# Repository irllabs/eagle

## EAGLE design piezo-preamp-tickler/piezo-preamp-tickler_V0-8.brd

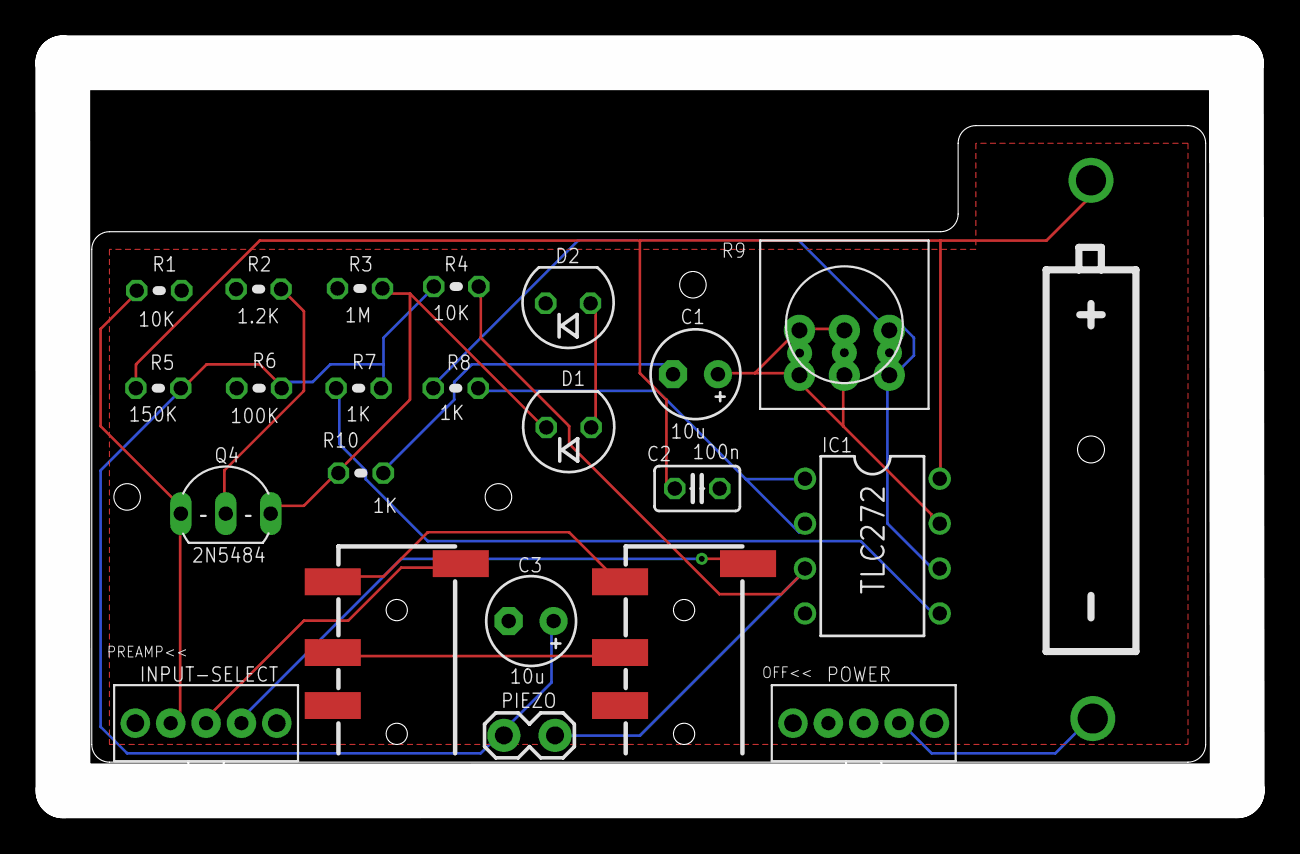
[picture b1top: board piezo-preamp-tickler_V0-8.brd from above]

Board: 2 copper layers, 66.4 x 41.2 mm, 23 parts (0 on the bottom side), 18 nets.

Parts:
BAT1: BATTERY-A23
C1, C3: 10u; E2,5-5
C2: 100n; C025-025X050
D1, D2: BB112; SOT54H
IC1: TLC272; DIL08
INPUT-SELECT: SPDT-SWITCH
ON/OFF: labl; SPDT-SWITCH
PIEZO: 1X02_LOCK
Q4: 2N5484; TO92-
R1, R4: 10K; 0204V
R2: 1.2K; 0204V
R3: 1M; 0204V
R5: 150K; 0204V
R6: 100K; 0204V
R7, R8, R10: 1K; 0204V
R9: TRIM-3386
TO-HEADSET: AUDIO-JACK3LGPADS; AUDIO-JACK-TRRS-SMD
TO-PHONE: AUDIO-JACK3LGPADS; AUDIO-JACK-TRRS-SMD

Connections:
GND: C2.1, C3.-, D2.C, IC1.4, ON/OFF.2, R1.1, R2.1, R3.1, R6.1, TO-HEADSET.RING2, TO-PHONE.RING2
unnamed: D1.A, D2.A
unnamed: BAT1.GND@1, ON/OFF.3
unnamed: Q4.2, R2.2
unnamed: IC1.5, R7.1
unnamed: C1.+, IC1.7, R9.1, R9.2, R9.4, R9.5
unnamed: IC1.6, R8.2, R9.3, R9.6
unnamed: C3.+, PIEZO.2, R4.2, R5.1, R6.2, R7.2
unnamed: IC1.3, PIEZO.1, R4.1
unnamed: D1.C, Q4.1, R3.2, R10.1
unnamed: C1.-, R10.2
unnamed: INPUT-SELECT.3, TO-HEADSET.EARTH
unnamed: TO-HEADSET.TIP, TO-PHONE.TIP
unnamed: IC1.1, IC1.2, R8.1
unnamed: TO-HEADSET.RING1, TO-PHONE.RING1
TO-PHONE: INPUT-SELECT.2, TO-PHONE.EARTH
V9V: BAT1.PWR@1, C2.2, IC1.8, R5.2
`DEL: INPUT-SELECT.1, Q4.3, R1.2

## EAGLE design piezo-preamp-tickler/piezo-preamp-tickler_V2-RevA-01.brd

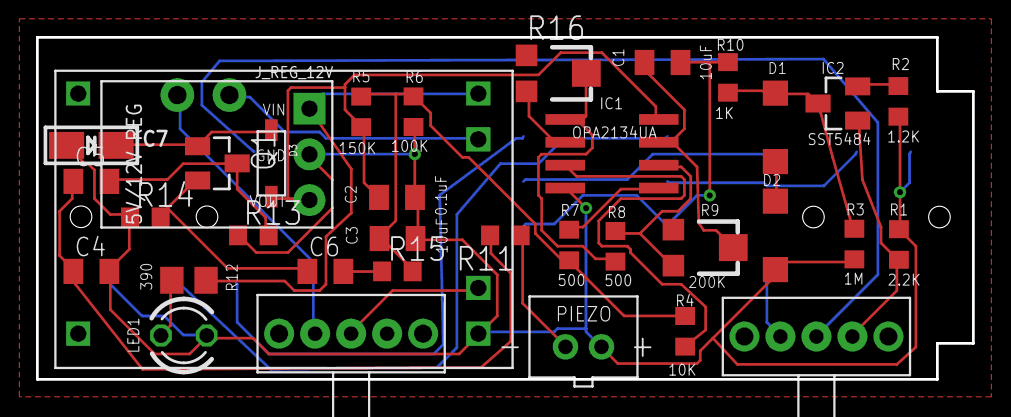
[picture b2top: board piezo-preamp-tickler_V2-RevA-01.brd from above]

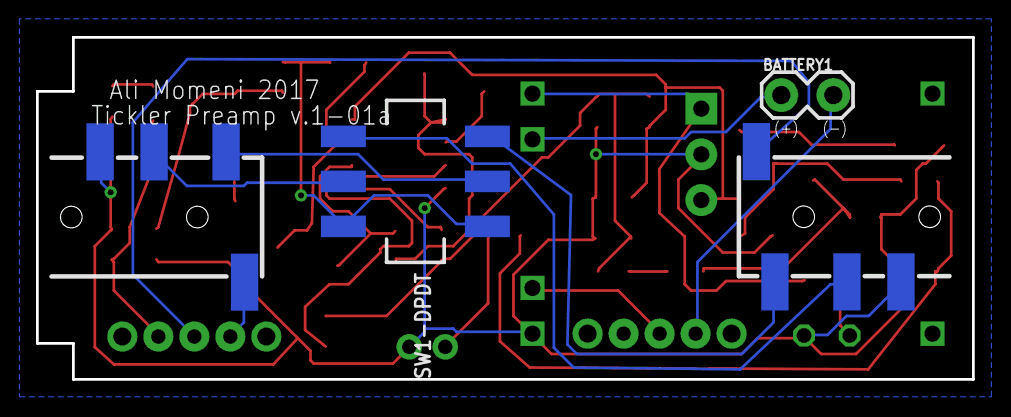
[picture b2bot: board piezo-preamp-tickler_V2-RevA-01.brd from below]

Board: 2 copper layers, 52.0 x 19.0 mm, 39 parts (4 on the bottom side), 31 nets.

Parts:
BATTERY1: 1X02_LOCK
C1, C3: 10uF; C0805K
C2: 0.1uF; C0805K
C4: 10p; C0805K
C5, C6: 0.033u; C0805K
C7: 3.3U; EIA3216-18/A-R
D1, D2: SOD123
D3: 1N4148; SOD-123
IC1: OPA2134UA; SO08
IC2: SST5484; SOT23
J_REG_12V: POLOLU_VOLTAGE_REGULATORS_3PIN; POLOLU_5V-12V_STEPUP_U3V12F5-U3V12F12
LED1: LED3MM
PIEZO: JST-PH-2-THM
POWER: SPDT; SWITCH_SPDT-TE-CONNECT
Q1: SST201; SOT23
R1: 2.2K; R0603
R2: 1.2K; R0603
R3: 1M; R0603
R4: 10K; R0603
R5: 150K; R0603
R6, R11: 100K; R0603
R7, R8: 500; R0603
R9, R16: 200K; TC33X
R10: 1K; R0603
R12: 390; R0805
R13: 10M; R0603
R14: 220K; R0603
R15: 13K; R0603
SW1-DPDT: OUTPUT-select; DPDT_SMT_JS202011SCQN
SW2-SPST: INPUT-select; SWITCH_SPDT-TE-CONNECT
TO-HEADSET: AUDIO-JACK3LGPADS; AUDIO-JACK-TRRS-SMD
TO-PHONE: AUDIO-JACK3LGPADS; AUDIO-JACK-TRRS-SMD
USB-LIPO-CHARGER: TP4056-MODULE; TP4056-LITHIUM-PROTECTED-MODULE

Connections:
+12V: C2.1, D3.A, IC1.8, J_REG_12V.VOUT, R5.2
GND: C2.2, C3.2, C4.2, C7.-, D2.C, IC1.4, J_REG_12V.GND, LED1.K, PIEZO.1, R1.1, R2.1, R3.1, R6.1, R13.1, R14.1, TO-HEADSET.RING2, TO-PHONE.RING2, USB-LIPO-CHARGER.OUT-
unnamed: D1.A, D2.A
unnamed: PIEZO.2, R11.1
unnamed: IC2.2, R2.2
unnamed: IC1.5, R7.1
unnamed: C1.1, IC1.7, R9.2
unnamed: IC1.6, R8.2, R9.3
unnamed: C3.1, R4.2, R5.1, R6.2, R7.2, R15.2
unnamed: IC1.3, R4.1
unnamed: D1.C, IC2.3, R3.2, R10.1
unnamed: C1.2, R10.2, SW1-DPDT.P$3, SW1-DPDT.P$4
unnamed: SW2-SPST.1, TO-HEADSET.EARTH
unnamed: SW1-DPDT.P$5, TO-HEADSET.TIP
unnamed: IC1.1, R8.1, R16.2
unnamed: SW1-DPDT.P$2, TO-HEADSET.RING1
unnamed: C4.1, C5.1, R11.2
unnamed: SW2-SPST.2, TO-PHONE.EARTH
unnamed: LED1.A, R12.1
unnamed: BATTERY1.1, USB-LIPO-CHARGER.B+
unnamed: POWER.2, USB-LIPO-CHARGER.B-
unnamed: BATTERY1.2, POWER.1
unnamed: C5.2, Q1.3, R13.2
unnamed: C6.1, Q1.2, R14.2
unnamed: C6.2, R15.1
unnamed: C7.+, D3.C, Q1.1
unnamed: SW1-DPDT.P$1, TO-PHONE.RING1
unnamed: SW1-DPDT.P$6, TO-PHONE.TIP
unnamed: IC1.2, R16.3
SELECT: IC2.1, R1.2, SW2-SPST.3
VBAT: J_REG_12V.VIN, R12.2, USB-LIPO-CHARGER.OUT+

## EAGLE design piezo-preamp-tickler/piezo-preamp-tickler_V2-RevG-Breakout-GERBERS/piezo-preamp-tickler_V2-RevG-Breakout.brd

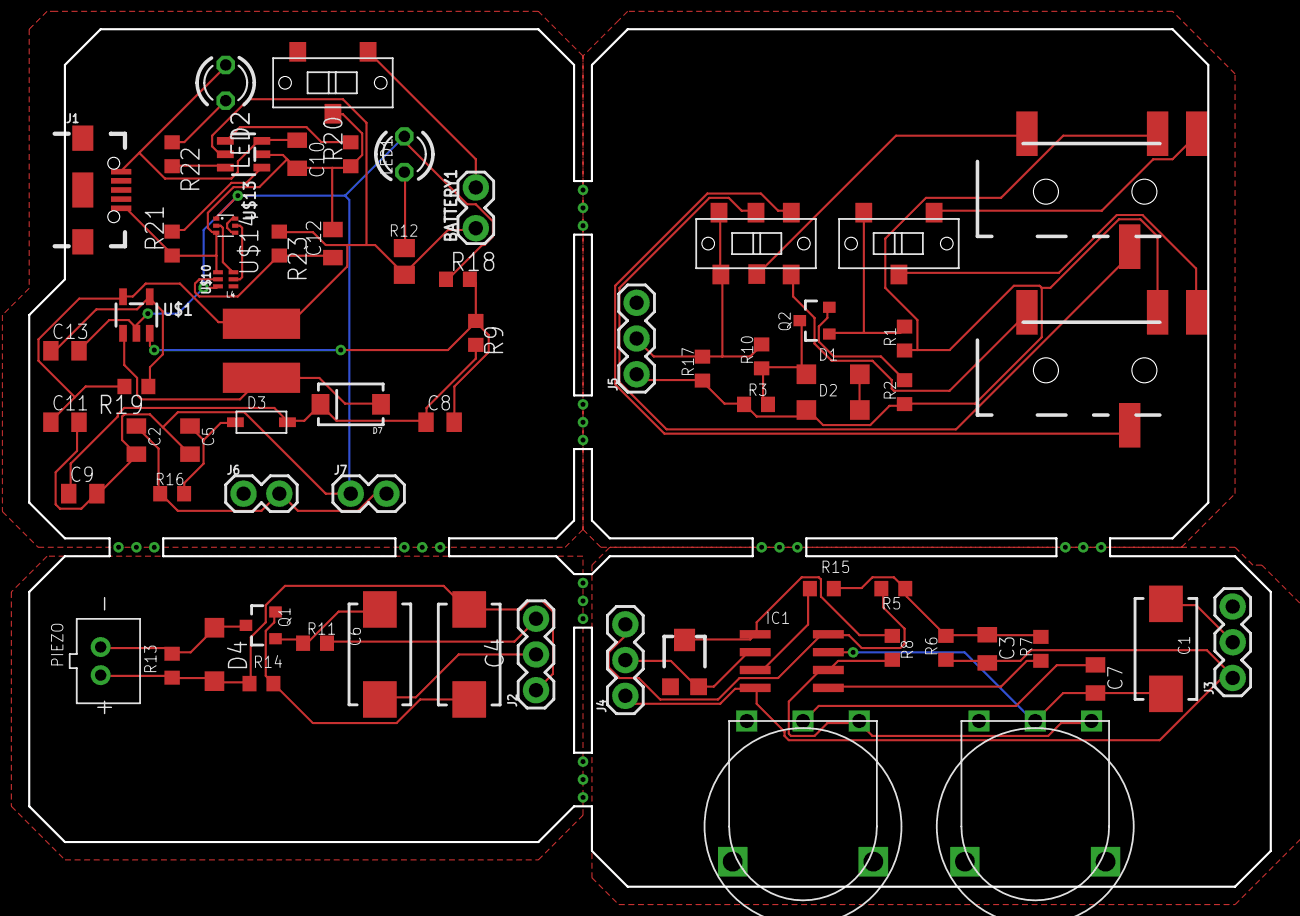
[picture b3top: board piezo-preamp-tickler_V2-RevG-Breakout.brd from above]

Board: 2 copper layers, 88.3 x 61.0 mm, 67 parts (0 on the bottom side), 49 nets.

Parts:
BATTERY1: 1X02_LOCK
C1: 47uF; CT7343
C2, C12, C13: 0.1uF; C0805K
C3, C5, C7, C9, C10, C11: 10uF; C0805K
C4: 150uF; CT7343
C6: 3.3uF; CT7343
C8: 22pF; C0805K
D1, D2, D4: SOD123
D3: 1N4148; SOD-123
D7: 10BQ015; SMA-DIODE
IC1: OPA2134UA; SO08
J1: USB-B-MICRO-SMD_RED_PASTE
J2, J3, J4, J5: 1X03
J6, J7: 1X02
L4: 2.7uH; CR54
LED1, LED2: LED3MM
PIEZO: JST-PH-2-THM
POWER: SPDT; SWITCH_SPDT_CL-SB-12B
Q1, Q2: J201SOT-23; SOT23-3
R1: 2.2K; R0603
R2, R14: 1.2K; R0603
R3: 1M; R0603
R4: 20K; TC33X
R5: 100K; R0603
R6: 150K; R0603
R7, R8, R10, R15: 1K; R0603
R9: 866k; R0603
R11, R17: 10K; R0603
R12: 390; R0805
R13: 10M; R0603
R16: 10; R0603
R18: 100k; R0603
R19: 15k; R0603
R20, R21: 10k; R0603
R22: 1k; R0603
R23: 330; R0603
SW2-SPST: INPUT-select; SWITCH_SPDT_CL-SB-12B
TO-HEADSET: AUDIO-JACK3LGPADS; AUDIO-JACK-TRRS-SMD
TO-PHONE: AUDIO-JACK3LGPADS; AUDIO-JACK-TRRS-SMD
U$1: SC4503; SOT23-5
U$2: SWITCH_DPDT; SWITCH_DPDT_CL-SB-22B
U$4, U$5: THUMBPOT14
U$10: BQ297X-BATTERY-MANAGER; WSON-6
U$13: BQ21040-LIPO-CHARGER; SOT23-6
U$14: DUAL-NFET-DMN2400; SOT-563

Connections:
+12V: C8.1, C9.1, D3.A, D7.C, R9.2
GND: C2.2, C5.2, C9.2, C11.2, C13.2, J7.1, LED1.K, R18.1, U$1.2, U$10.6, U$14.1
GND1: C10.2, C12.2, J1.GND, POWER.P$2, R20.1, R21.1, U$10.4, U$13.5, U$14.3
unnamed: D1.A, D2.A
unnamed: D4.C, PIEZO.2, Q1.3, R13.2
unnamed: Q2.2, R2.2
unnamed: IC1.5, R7.1
unnamed: C1.+, C7.2, IC1.7, U$4.P$2
unnamed: IC1.6, R8.2, U$4.P$1, U$5.P$1
unnamed: C6.+, Q1.1, R11.1
unnamed: D1.C, Q2.3, R3.2, R10.1
unnamed: J5.2, R10.2, R17.2, U$2.1, U$2.4
unnamed: SW2-SPST.P$1, TO-HEADSET.EARTH
unnamed: TO-HEADSET.TIP, U$2.2
unnamed: C4.+, Q1.2, R14.2
unnamed: TO-HEADSET.RING1, U$2.5
unnamed: C5.1, D3.C, R16.2
unnamed: SW2-SPST.P$2, TO-PHONE.EARTH
unnamed: LED1.A, R12.1
unnamed: IC1.2, J4.2, R4.3
unnamed: BATTERY1.2, POWER.P$1
unnamed: IC1.3, R15.1
unnamed: C3.1, R5.1, R6.2, R7.2, R15.2
unnamed: IC1.1, R4.2, R8.1
unnamed: J2.3, R11.2
unnamed: TO-PHONE.RING1, U$2.6
unnamed: TO-PHONE.TIP, U$2.3
unnamed: C6.-, J2.2
unnamed: C13.1, R19.1, U$1.4
unnamed: C8.2, R9.1, R18.2, U$1.3
unnamed: C7.1, U$5.P$2
unnamed: D7.A, L4.P$2, U$1.1
unnamed: R22.2, U$13.3
unnamed: C12.1, R23.2, U$10.5
unnamed: R20.2, U$13.1
unnamed: C1.-, J3.2
unnamed: U$14.4, U$14.6
unnamed: R21.2, U$13.4
unnamed: U$10.2, U$14.5
unnamed: LED2.K, R22.1
unnamed: U$10.3, U$14.2
unnamed: IC1.8, J4.3, R5.2
unnamed: C2.1, J6.2, J7.2, R16.1
unnamed: C4.-, D4.A, J2.1, PIEZO.1, R13.1, R14.1
unnamed: D2.C, J5.1, R1.1, R2.1, R3.1, R17.1, TO-HEADSET.RING2, TO-PHONE.RING2
unnamed: C3.2, IC1.4, J3.1, J4.1, R6.1
SELECT: Q2.1, R1.2, SW2-SPST.P$3
V+: C10.1, J1.VBUS, LED2.A, U$13.6
VBAT: BATTERY1.1, C11.1, L4.P$1, R12.2, R19.2, R23.1, U$1.5, U$13.2

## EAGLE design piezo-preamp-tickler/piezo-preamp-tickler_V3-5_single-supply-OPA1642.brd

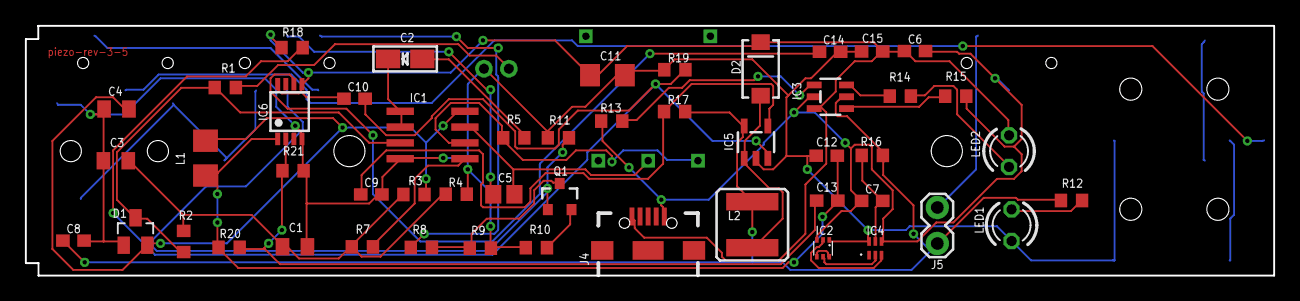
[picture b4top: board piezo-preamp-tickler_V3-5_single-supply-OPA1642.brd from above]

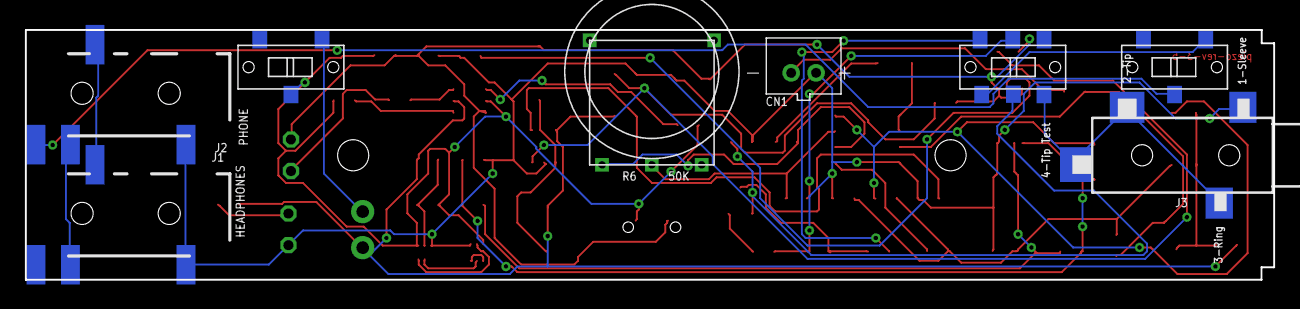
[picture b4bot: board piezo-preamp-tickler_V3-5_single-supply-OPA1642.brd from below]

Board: 2 copper layers, 100.3 x 20.1 mm, 58 parts (8 on the bottom side), 39 nets.

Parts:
C1: 10uF; C0805K
C2: 100uF; EIA3216-18/A-R
C3, C4: 0.1uF; C0805K
C5: 10uF; C0805
C6, C8, C12, C15: 10uF; C0603
C7: 0.1uF; C0603
C9: 56nF; C0603
C10: 2.2pF; C0603
C11: 68uF; C1206
C13, C14: 10nF; C0603
CN1: JST-PH-2-THM
D1: BAT54S; SOT23
D2: 10BQ015; SMA-DIODE
IC1: OPA1642; SO08
IC2: DMN2400; SOT-563
IC3: BQ21040; SOT23-6
IC4: BQ297X; WSON-6
IC5: SC4503; SOT23-5
IC6: TPS7A49; MSOP-8
J1: HEADPHONES; TRRS_SJ-43514-SMT-TR
J2: PHONE; TRRS_SJ-43514-SMT-TR
J3: Mixer; TRS_SJ-3524-SMT
J4: USB-B-MICRO-SMD_RED_PASTE
J5: Battery; 1X02_LOCK
L1: 100uH; L3225P
L2: 2.7uH; CR54
LED1: Power; LED3MM
LED2: Charge; LED3MM
Q1: MMBFJ201; SOT23-3
R1, R3, R4: 100K; R0603
R2: 10M; R0603
R5, R7: 220; R0603
R6: 50K; POT-THUMB-14MM_ALPHA-RV100F-30-4K1B-B10K-B301
R8: 1K; R0603
R9, R18: 1M; R0603
R10: 1.2K; R0603
R11: 2.2K; R0603
R12: 390; R0603
R13, R15: 10k; R0603
R14: 1k; R0603
R16: 330; R0603
R17: 15k; R0603
R19, R21: 100k; R0603
R20: 91.2k; R0603
SW1: SWITCH_DPDT; SWITCH_DPDT_CL-SB-22B
SW2: INPUT-select; SWITCH_SPDT_CL-SB-12B
SW3: SPDT; SWITCH_SPDT_CL-SB-12B

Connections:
+12V: C12.1, C13.1, IC6.1, L1.1, R20.1
GND: C1.2, C3.2, C4.2, C8.2, C9.2, C11.2, C12.2, C14.2, C15.2, CN1.1, D1.1, IC1.4, IC2.1, IC4.6, IC5.2, IC6.4, J1.TIP, J2.TIP, J3.1, LED1.K, R4.1, R9.1, R10.1, R11.1, R19.1, R21.2
GND2: C6.2, C7.1, IC2.3, IC3.5, IC4.4, J4.GND, R13.1, R15.1, SW3.P$2
unnamed: CN1.2, R1.1
unnamed: Q1.2, R10.2
unnamed: IC1.5, R7.1
unnamed: C5.1, IC1.7, R6.P$2
unnamed: IC1.6, R5.2, R6.P$1
unnamed: D1.3, IC1.3, R1.2, R2.2
unnamed: Q1.3, R8.1, R9.2
unnamed: R8.2, SW1.4
unnamed: J3.2, J3.3, J3.4, SW1.3
unnamed: J1.RING1, J2.RING1
unnamed: C2.-, R5.1
unnamed: J1.RING2, J2.RING2
unnamed: C5.2, SW1.5
unnamed: J2.EARTH, SW2.P$2
unnamed: LED1.A, R12.1
unnamed: SW1.1, SW2.P$1
unnamed: J5.2, SW3.P$1
unnamed: LED2.K, R14.1
unnamed: C1.1, C3.1, R2.1, R3.1, R4.2, R7.2
unnamed: C2.+, IC1.1, IC1.2
unnamed: C4.1, D1.2, IC1.8, L1.2, R3.2
unnamed: C13.2, IC6.2, R20.2, R21.1
unnamed: IC3.3, R14.2
unnamed: C14.1, IC6.6
unnamed: C9.1, IC5.4, R17.1
unnamed: C10.2, IC5.3, R18.1, R19.2
unnamed: IC3.1, R15.2
unnamed: D2.A, IC5.1, L2.P$2
unnamed: IC3.4, R13.2
unnamed: C7.2, IC4.5, R16.2
unnamed: IC2.4, IC2.6
unnamed: IC2.5, IC4.2
unnamed: IC2.2, IC4.3
SELECT: Q1.1, R11.2, SW1.2
V+: C6.1, C10.1, C11.1, C15.1, D2.C, IC3.6, IC6.5, IC6.8, J4.VBUS, LED2.A, R18.2
VBAT: C8.1, IC3.2, IC5.5, J5.1, L2.P$1, R12.2, R16.1, R17.2

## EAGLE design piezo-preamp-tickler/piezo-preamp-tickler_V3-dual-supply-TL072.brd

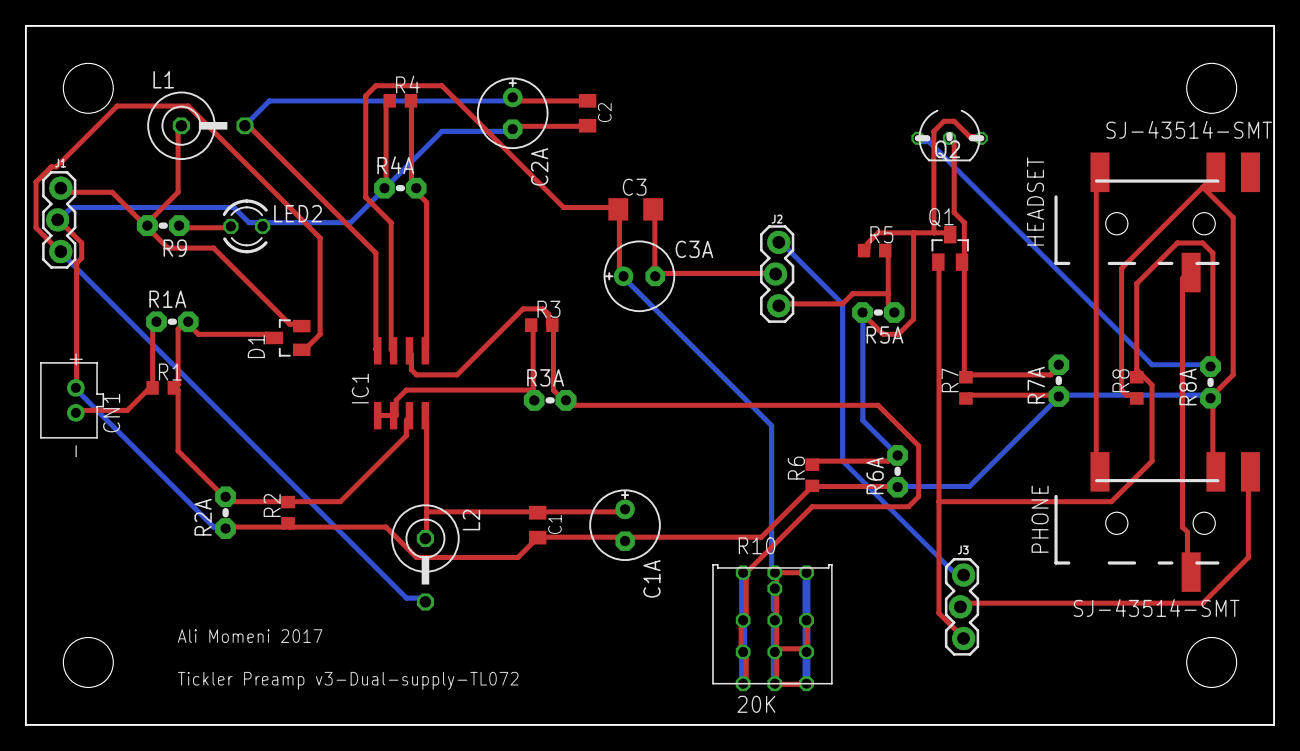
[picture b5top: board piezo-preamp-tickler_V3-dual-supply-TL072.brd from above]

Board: 2 copper layers, 100.0 x 56.0 mm, 37 parts (0 on the bottom side), 21 nets.

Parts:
C1, C2: 0.1uF; C0805K
C1A, C3A: 10uF; E2,5-6E
C2A: 0.1uF; E2,5-6E
C3: 10uF; C1206
CN1: JST-PH-2-THM
D1: BAT54S; SOT23
HEADSET: SJ-43514-SMT; TRRS_SJ-43514-SMT-TR
IC1: TL072; SO08
J1: 1X03_LOCK
J2, J3: phone/mixer-switch; 1X03_LOCK
L1, L2: 100uH; LBC-SE
LED2: LED3MM
PHONE: SJ-43514-SMT; TRRS_SJ-43514-SMT-TR
Q1: MMBFJ201; SOT23
Q2: 2N5486; TO92-
R1: 100K; R0603
R1A: 100K; 0204V
R2: 10M; R0603
R2A: 10M; 0204V
R3, R4: 220; R0603
R3A, R4A: 220; 0204V
R5: 1K; R0603
R5A: 1K; 0204V
R6: 1M; R0603
R6A: 1M; 0204V
R7: 1.2K; R0603
R7A, R9: 1.2K; 0204V
R8: 2.2K; R0603
R8A: 2.2K; 0204V
R10: 20K; TRIMPOT-MULTI

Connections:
+12V: D1.2, J1.1, L1.1, R9.2
-12V: D1.1, J1.3, L2.2
GND: C1.2, C1A.-, C2.2, C2A.-, CN1.1, HEADSET.RING2, J1.2, LED2.K, PHONE.RING2, R2.1, R2A.1, R4.1, R4A.1, R6.1, R6A.1, R7.1, R7A.1, R8.1, R8A.1
unnamed: IC1.1, IC1.2, R3.1, R3A.1
unnamed: J2.3, R5.2, R5A.1
unnamed: C1.1, C1A.+, IC1.4, L2.1
unnamed: LED2.A, R9.1
unnamed: IC1.5, R4.2, R4A.2
unnamed: IC1.6, R3.2, R3A.2, R10.P$1, R10.P$3, R10.P$4, R10.P$6, R10.P$9
unnamed: C3.2, C3A.-, J2.2
unnamed: CN1.2, R1.1, R1A.1
unnamed: Q1.2, Q2.2, R7.2, R7A.2
unnamed: C3.1, C3A.+, IC1.7, R10.P$10, R10.P$12, R10.P$13, R10.P$15, R10.P$16, R10.P$18, R10.P$20, R10.P$21, R10.P$22, R10.P$24, R10.P$27
unnamed: C2.1, C2A.+, IC1.8, L1.2
unnamed: D1.3, IC1.3, R1.2, R1A.2, R2.2, R2A.2
unnamed: Q1.3, Q2.1, R5.1, R5A.2, R6.2, R6A.2
unnamed: J2.1, J3.1
unnamed: HEADSET.TIP, PHONE.TIP
unnamed: HEADSET.RING1, PHONE.RING1
unnamed: J3.2, PHONE.EARTH
SELECT1: J3.3, Q1.1, Q2.3, R8.2, R8A.2

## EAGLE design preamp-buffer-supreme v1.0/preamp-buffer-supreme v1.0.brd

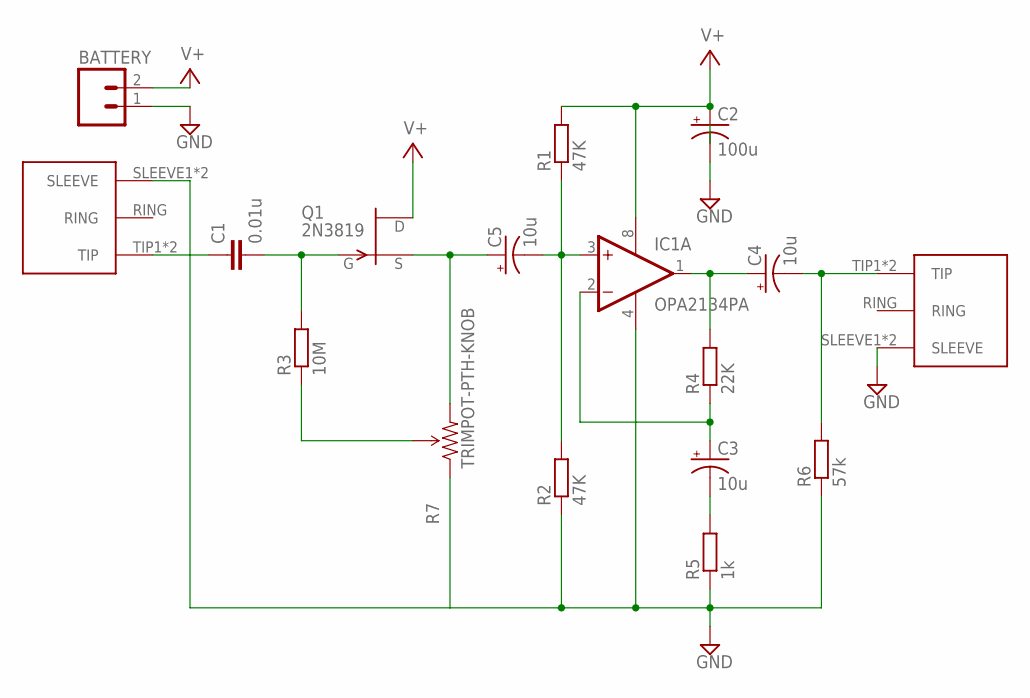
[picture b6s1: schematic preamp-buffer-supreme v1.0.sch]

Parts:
BATTERY: M02PTH; 1X02
C1: 0.01u; C5B3
C2: 100u; CPOL-RADIAL-10UF-25V
C3, C4, C5: 10u; CPOL-RADIAL-10UF-25V
IC1: OPA2134PA; DIL08
Q1: 2N3819; TO92
R1, R2: 47K; 0204/7
R3: 10M; 0204/7
R4: 22K; 0204/7
R5: 1k; 0204/7
R6: 57k; 0204/7
R7: TRIMPOT-PTH-KNOB; 3386U
U$2, U$3: 3.5MM-STEREO-JACK

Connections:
GND: BATTERY.1, C2.2 (-), IC1.4 (V-), R2.1, R5.1, R6.1, R7.1 (CCW), U$2.SLEEVE1 (SLEEVE), U$2.SLEEVE2 (SLEEVE), U$3.SLEEVE1 (SLEEVE), U$3.SLEEVE2 (SLEEVE)
JFET-GATE: C1.2, Q1.2 (G), R3.2
JFET-SOURCE: C5.1 (+), Q1.3 (S), R7.3 (CW)
unnamed: C1.1, U$2.TIP1 (TIP), U$2.TIP2 (TIP)
unnamed: R3.1, R7.2 (WIPER)
unnamed: C5.2 (-), IC1.3 (+IN), R1.1, R2.2
unnamed: C4.1 (+), IC1.1 (OUT), R4.2
unnamed: C3.2 (-), R5.2
unnamed: C4.2 (-), R6.2, U$3.TIP1 (TIP), U$3.TIP2 (TIP)
unnamed: C3.1 (+), IC1.2 (-IN), R4.1
V+: BATTERY.2, C2.1 (+), IC1.8 (V+), Q1.1 (D), R1.2

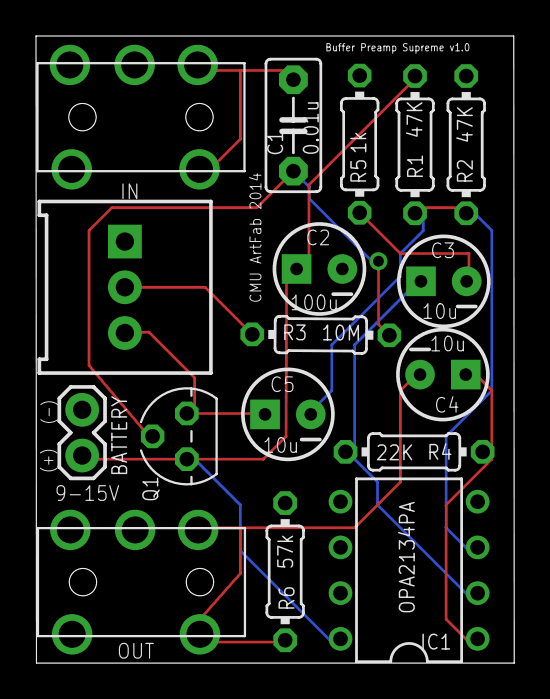
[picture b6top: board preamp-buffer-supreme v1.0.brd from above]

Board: 2 copper layers, 26.6 x 34.8 mm, 17 parts (0 on the bottom side), 11 nets.

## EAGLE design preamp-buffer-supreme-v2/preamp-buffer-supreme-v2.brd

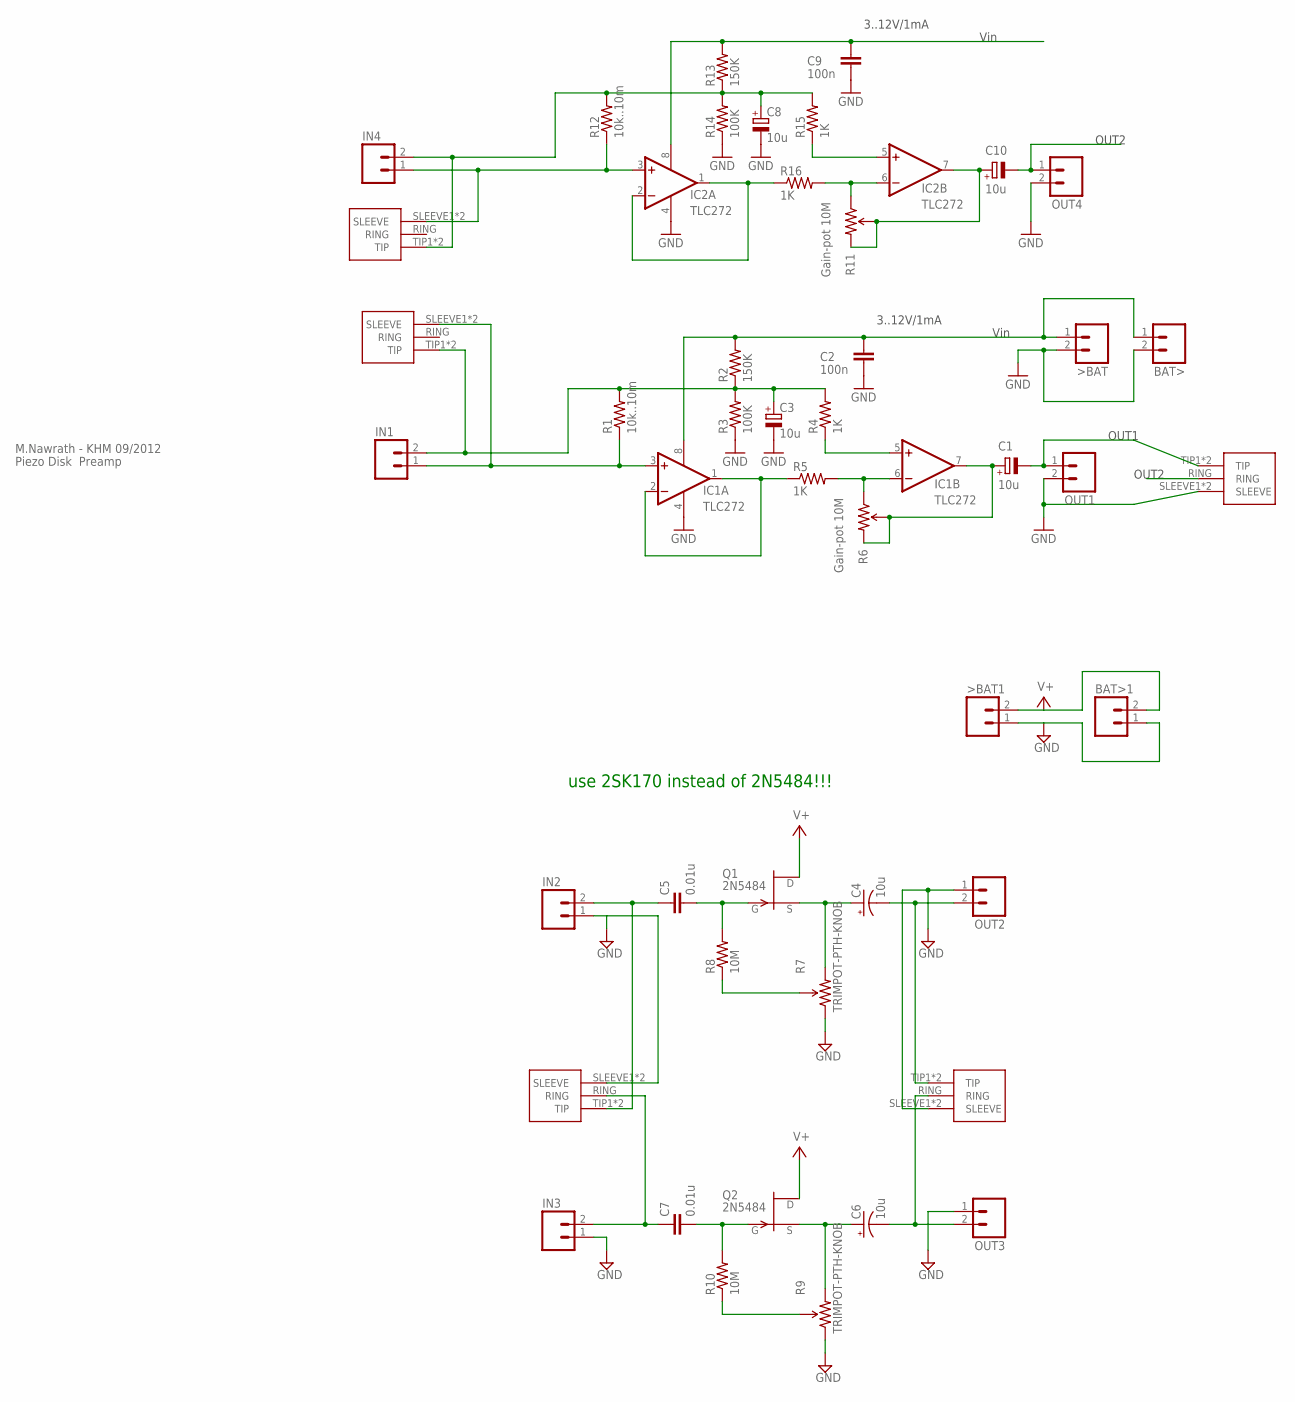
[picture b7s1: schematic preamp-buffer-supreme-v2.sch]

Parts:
>BAT: M02LOCK; 1X02_LOCK
>BAT1: M02PTH; 1X02
BAT>: M02LOCK; 1X02_LOCK
BAT>1: M02PTH; 1X02
C1, C3, C8, C10: 10u; E2,5-5
C2, C9: 100n; C025-025X050
C4, C6: 10u; CPOL-RADIAL-10UF-25V
C5, C7: 0.01u; C5B3
IC1, IC2: TLC272; DIL08
IN1, IN2, IN3, IN4: M02LOCK; 1X02_LOCK
OUT1, OUT2, OUT3, OUT4: M02LOCK; 1X02_LOCK
OUT1-TRS: 1/8"-F-STEREO-PCB
Q1, Q2: 2N5484; TO92-
R1, R12: 10k..10m; 0204V
R2, R13: 150K; 0204V
R3, R14: 100K; 0204V
R4, R5, R15, R16: 1K; 0204V
R6, R11: Gain-pot 10M; 3386U
R7, R9: TRIMPOT-PTH-KNOB; 3386U
R8, R10: 10M; 0204V
U$1, U$2, U$3, U$4: 1/8"-F-STEREO-PCB

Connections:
CH1: C4.2 (-), OUT2.2, U$1.TIP1 (TIP), U$1.TIP2 (TIP)
CH2: C6.2 (-), OUT3.2, U$1.RING
GND: >BAT.2, >BAT1.1, BAT>.2, BAT>1.1, C2.1, C3.-, C8.-, C9.1, IC1.4 (V-), IC2.4 (V-), IN2.1, IN3.1, OUT1.2, OUT1-TRS.SLEEVE1 (SLEEVE), OUT1-TRS.SLEEVE2 (SLEEVE), OUT2.1, OUT3.1, OUT4.2, R3.1, R7.1 (CCW), R9.1 (CCW), R14.1, U$1.SLEEVE1 (SLEEVE), U$1.SLEEVE2 (SLEEVE), U$3.SLEEVE1 (SLEEVE), U$3.SLEEVE2 (SLEEVE)
JFET-GATE: C5.2, Q1.1 (G), R8.2
JFET-GATE1: C7.2, Q2.1 (G), R10.2
JFET-SOURCE: C4.1 (+), Q1.2 (S), R7.3 (CW)
JFET-SOURCE1: C6.1 (+), Q2.2 (S), R9.3 (CW)
unnamed: C3.+, IN1.2, R1.2, R2.1, R3.2, R4.2, U$2.TIP1 (TIP), U$2.TIP2 (TIP)
unnamed: IC1.6 (-IN), R5.2, R6.1 (CCW)
unnamed: R7.2 (WIPER), R8.1
unnamed: IC1.5 (+IN), R4.1
unnamed: C1.+, IC1.7 (OUT), R6.2 (WIPER), R6.3 (CW)
unnamed: C5.1, IN2.2, U$3.TIP1 (TIP), U$3.TIP2 (TIP)
unnamed: IC1.3 (+IN), IN1.1, R1.1, U$2.SLEEVE1 (SLEEVE), U$2.SLEEVE2 (SLEEVE)
unnamed: R9.2 (WIPER), R10.1
unnamed: C7.1, IN3.2, U$3.RING
unnamed: IC2.1 (OUT), IC2.2 (-IN), R16.1
unnamed: IC2.5 (+IN), R15.1
unnamed: IC1.1 (OUT), IC1.2 (-IN), R5.1
unnamed: C10.+, IC2.7 (OUT), R11.2 (WIPER), R11.3 (CW)
unnamed: IC2.6 (-IN), R11.1 (CCW), R16.2
unnamed: C8.+, IN4.2, R12.2, R13.1, R14.2, R15.2, U$4.TIP1 (TIP), U$4.TIP2 (TIP)
unnamed: IC2.3 (+IN), IN4.1, R12.1, U$4.SLEEVE1 (SLEEVE), U$4.SLEEVE2 (SLEEVE)
OUT1: C1.-, OUT1.1, OUT1-TRS.TIP1 (TIP), OUT1-TRS.TIP2 (TIP)
OUT2: C10.-, OUT1-TRS.RING, OUT4.1
V+: >BAT1.2, BAT>1.2, Q1.3 (D), Q2.3 (D)
VIN: >BAT.1, BAT>.1, C2.2, C9.2, IC1.8 (V+), IC2.8 (V+), R2.2, R13.2

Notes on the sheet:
Piezo Disk Preamp
M.Nawrath - KHM 09/2012
3..12V/1mA
use 2SK170 instead of 2N5484!!!
Vin
OUT2
OUT1

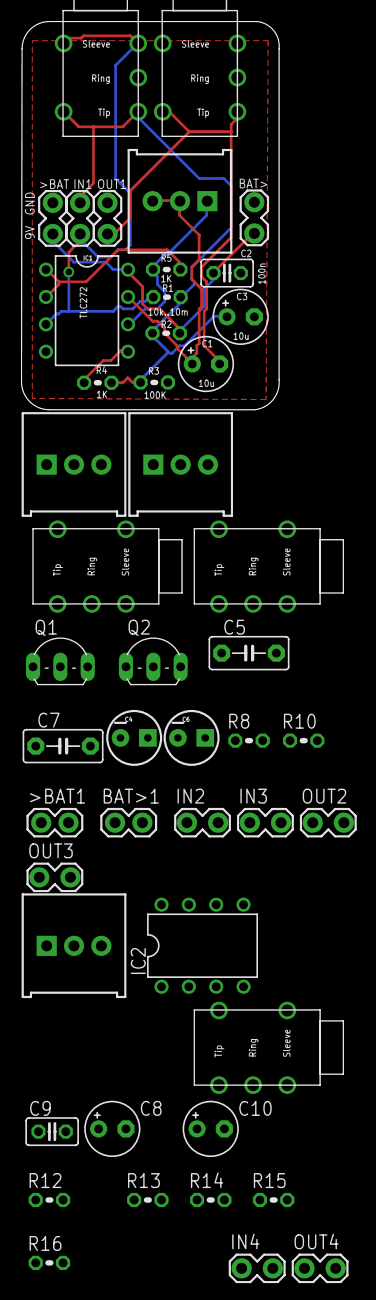
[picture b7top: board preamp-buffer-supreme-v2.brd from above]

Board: 2 copper layers, 23.9 x 36.1 mm, 47 parts (0 on the bottom side), 27 nets.

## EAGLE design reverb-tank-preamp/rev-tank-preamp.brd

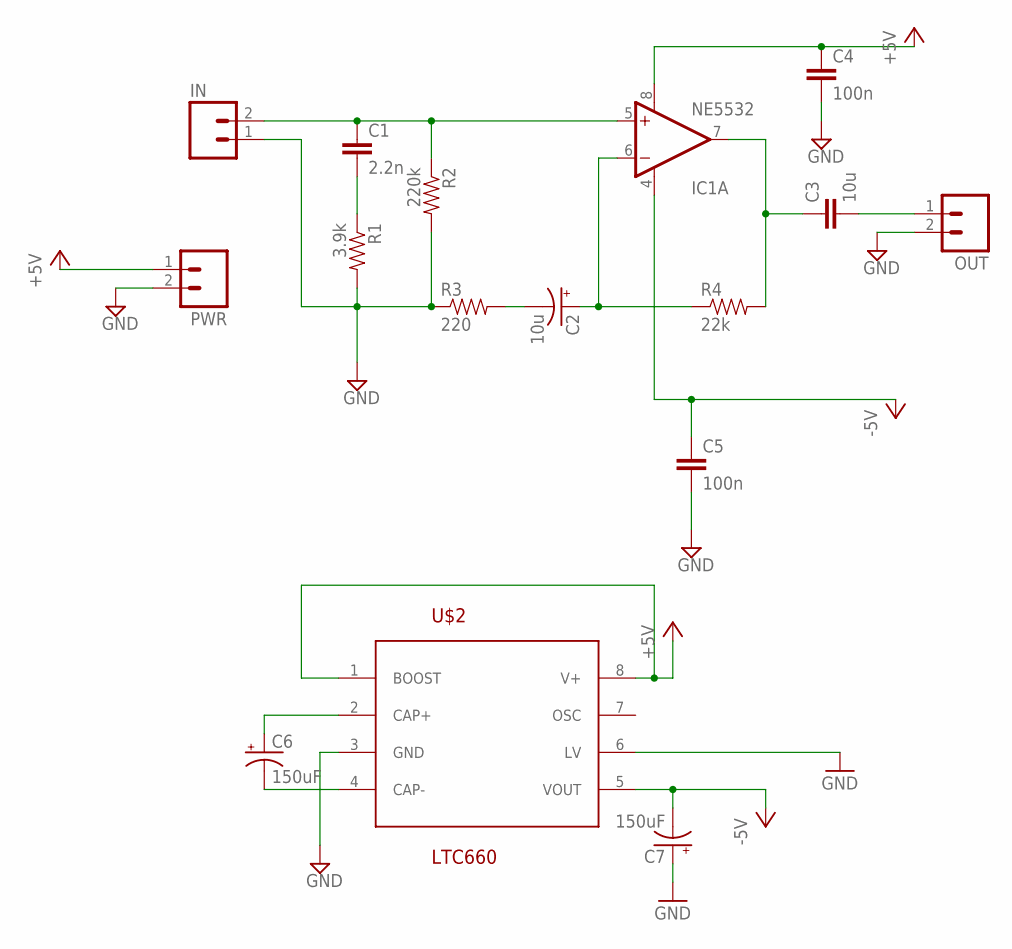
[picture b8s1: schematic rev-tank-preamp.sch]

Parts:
C1: 2.2n; CAP-PTH-5MM
C2: 10u; CPOL-RADIAL-10UF-25V
C3: 10u; CAP-PTH-5MM
C4, C5: 100n; CAP-PTH-5MM
C6, C7: 150uF; CPOL-RADIAL-100UF-25V
IC1: NE5532; DIP08
IN: M02PTH; 1X02
OUT: M02PTH; 1X02
PWR: M02PTH; 1X02
R1: 3.9k; 1/6W-RES
R2: 220k; 1/6W-RES
R3: 220; 1/6W-RES
R4: 22k; 1/6W-RES
U$2: LTC660; SO08

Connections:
+5V: C4.1, IC1.8 (V+), PWR.1, U$2.1 (BOOST), U$2.8 (V+)
-5V: C5.1, C7.2 (-), IC1.4 (V-), U$2.5 (VOUT)
GND: C4.2, C5.2, C7.1 (+), IN.1, OUT.2, PWR.2, R1.2, R2.2, R3.1, U$2.3 (GND), U$2.6 (LV)
unnamed: C1.1, IC1.5 (+IN), IN.2, R2.1
unnamed: C1.2, R1.1
unnamed: C6.1 (+), U$2.2 (CAP+)
unnamed: C2.1 (+), IC1.6 (-IN), R4.1
unnamed: C2.2 (-), R3.2
unnamed: C3.2, OUT.1
unnamed: C6.2 (-), U$2.4 (CAP-)
unnamed: C3.1, IC1.7 (OUT), R4.2

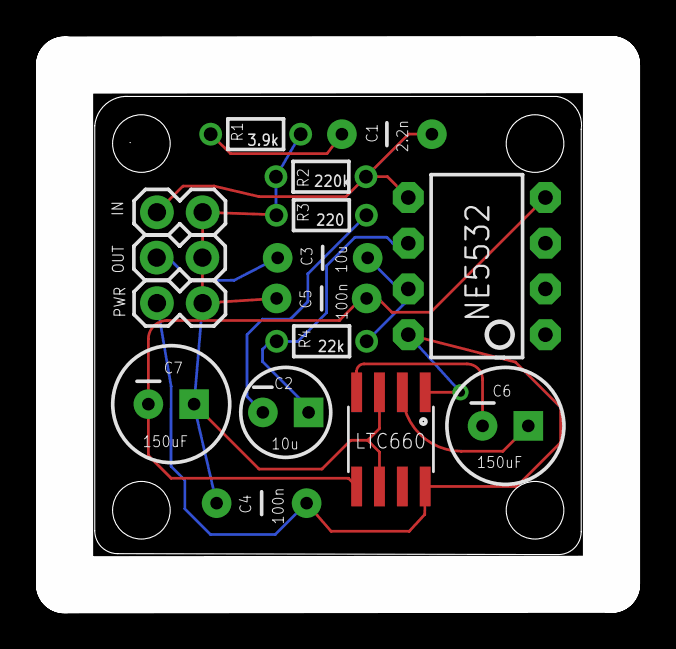
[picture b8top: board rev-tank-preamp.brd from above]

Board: 2 copper layers, 30.4 x 28.9 mm, 16 parts (0 on the bottom side), 11 nets.

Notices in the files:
parts and their libraries:
SparkFun-Connectors: Licensing: Creative Commons ShareAlike 4.0 International - https://creativecommons.org/licenses/by-sa/4.0
microbuilder: This work is placed in the public domain, and may be freely used for commercial and non-commercial work with the following conditions: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
